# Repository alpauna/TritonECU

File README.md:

# TritonECU

Standalone engine and transmission controller for **Ford modular V8s of the
EEC-V era** — replacing the factory PCM.

Developed against a **1999 F-150 4WD, 5.4L Triton 2V, 4R70W**, but the
architecture is the modular family rather than one truck: 4.6L and 5.4L 2V
share the crank trigger, the sensor set, the SCP bus and the connector, so
Mustangs and other EEC-V modular applications of the period are the same
problem with a different calibration.

Built on an **STM32F767ZI**. Rewritten from scratch on the `rebuild` branch;
the previous ESP32-S3 firmware is described in
[`docs/legacy-esp32s3-README.md`](docs/legacy-esp32s3-README.md) and still
lives on `main`.

**What is vehicle-specific and what is not:**

| Portable across EEC-V modulars | Specific to this truck |
|---|---|
| 36-1 VR crank decode, cam sync | firing order, displacement |
| EEC-V 104-pin connector and pinout | 4R70W shift logic (4R100 differs) |
| SCP / J1850 PWM bus | 4x4 transfer case inputs |
| Ignition and injection output stages | VE and spark tables |
| Sensor conditioning and protection | |

---

## Status

| Milestone | | |
|---|---|---|
| **M0** Board bring-up | ✅ | 216 MHz, 2 MB flash, verified from the chip's own ID registers |
| **M1** Storage + config | ✅ | SD on SPI4, JSON config, persists across resets |
| **M2** Analog front end | ✅ | AD7606 reading known signals within tolerance |
| **M3** Crank sync | ◐ | decode logic proven — 10 native tests; **VR board on order**, CKP sensor + pigtail ordered |
| **M4** Cam sync | ◐ | logic proven — 6 native tests; **CMP sensor + pigtail ordered** — same connector as CKP |
| **M5** Spark output | ◐ | scheduler proven — 12 native tests |
| **M6+** Injection, closed loop, SCP, transmission | ○ | |
| **ECU carrier board** | ○ | **the largest piece left.** Fully specified in [`schematic-ecu-v1.txt`](docs/Schematics/schematic-ecu-v1.txt) — 736 lines, every part chosen — but **not yet captured as a schematic or laid out**. Envelope and the height constraint: [`carrier-envelope.md`](docs/carrier-envelope.md) |
| **Power board V1** | 🔒 | **released and frozen** — tagged `power-v1-released`, [`Schematics/README`](docs/Schematics/README.md) |
| **Power board V2** | ✅ | V1 **+ one part**: `C1` 100 nF 1206 X7R **200 V** across B+/PGND at the connector — a 19 mm² loop against D1's 131. Reviewed clean, **ready to fab** |
| **VR board V1** | ✅ | 4 channels, 2 × MAX9926 Mode A2 — reviewed clean, **fabricating** |
| **VR test rig** | ◐ | all dimensions measured; 9 of 10 parts ready to print, [STLs](hardware/vr-test-rig/stl/) + [BOM](hardware/vr-test-rig/BOM.md). Parts ordered bar the stepper |
| **VR rig firmware** | ✅ | RP2040 PIO step generator with a cranking profile — builds clean, [`firmware/`](hardware/vr-test-rig/firmware/) |
| **2N7002 driver board** | ✅ | 3.3 V → DM542 opto inputs, reviewed clean from Gerbers — [`hardware/2N7002 Driver/`](hardware/2N7002%20Driver/) |
| **Knock front end** | ◐ | **next build after the VR board** — schematic, net list and BOM drawn, [`knock-front-end-schematic.md`](docs/Schematics/knock-front-end-schematic.md) |
| **EEC-V connector** | ✅ | sourcing solved — Ranger donor + the TE controlled drawing |
| **Enclosure** | ◐ | **cabin, behind the glovebox**, connector face through the firewall — vent on the cabin side, [`enclosure.md`](docs/enclosure.md) |
| **Carrier template** | ✅ | printable measurement jig for the donor case floor — captures the mounting-boss pattern the layout is waiting on, [`hardware/carrier-template/`](hardware/carrier-template/) |
| **Harness label** | ✅ | printed plate for the always-hot battery lead and the four added pins — [STL](hardware/harness-label/stl/label.stl) + [`README`](hardware/harness-label/README.md) |
| **PSU platform** | ✅ | Z-bracket that stands the supply module off the surface — 74.5 × 92 × 51, [`hardware/psu-platform/`](hardware/psu-platform/) |

**28 native unit tests passing.** The decode, cam-sync and spark-scheduling
modules are `<stdint.h>`-only and testable without hardware — which is how M3–M5
were proven before the sensors existed.

```bash
pio test -e native              # logic, no hardware
pio run -e nucleo -t upload     # flash the board
```

## Why it is being rebuilt

The previous firmware worked, but was written against an ESP32-S3 that was
never in a truck, and one of its structural decisions turned out to be wrong:
**coils and injectors were driven through MCP23S17 SPI expanders.**

At 6000 rpm one crank degree is **27.8 µs**. An SPI transaction is several
microseconds at best, is not deterministic, and cannot be driven from a
hardware timer. Spark timing cannot live behind a port expander. That is not a
bug to patch — it changes ignition, injection and the pin map together.

Proven pieces get ported forward deliberately. Everything else earns its place
again. See [`docs/roadmap.md`](docs/roadmap.md).

## Hardware

Design is frozen — [`docs/v1-scope.md`](docs/v1-scope.md) is the build list.

**Two boards are finished.** Schematics, BOMs and Gerbers are all version
controlled in [`docs/Schematics/`](docs/Schematics/) — the fab outputs, not just
pictures of them.

| Board | Size | Review |
|---|---|---|
| **Power V1** | 76.58 × 46.74 mm, 4 layer | [`review-power-v1-bom-gerbers.md`](docs/review-power-v1-bom-gerbers.md) |
| **VR V1** | 35.43 × 33.91 mm, 2 layer | [`review-vr-v1.md`](docs/review-vr-v1.md) |

Both reviews were **measured out of the Gerbers** — copper polygon areas, via
positions, pad geometry and the flying-probe netlist — rather than read off a
render. That is how the MAX25239 footprint, Q2's thermal path and the output-cap
pour were actually checked. The earlier schematic-only pass on the power board
is [`schematic-review-power-v2.md`](docs/schematic-review-power-v2.md).

| Block | Part |
|---|---|
| MCU | STM32F767ZI (Nucleo-144 now, raw chip later) |
| Input protection | LTC4364-2 — reverse polarity, load dump, overcurrent, brownout holdup |
| Pass element | IRF540NS (D2Pak) on HGATE — planar, published SOA, 20 tented vias into 1.14 in² of B+ |
| 5 V rail | MAX25239AFF**A** buck-boost, 2.1 MHz, spread spectrum, 2.2 µH |
| 3.3 V rail | TLV62085 buck from 5 V, 2.4 MHz, 500 nH |
| ADC reference | MAX6070AAUT25, 2.5 V, gated for sleep |
| Battery sense | INA238 on the LTC4364's own 10 mΩ / 1 % / 50 ppm shunt |
| Analog in | **ADS8588H** — 8 ch, 16-bit, 500 kSPS simultaneous, ±10 V, **9 kV input clamp**, −40…+125 °C |
| Analog in *(bench)* | **Tokmas AD7606BSTZ** — same LQFP-64 footprint, 200 kSPS, already in hand |
| Crank / cam / OSS | 2 × MAX9926 Mode A2 — 4 channels, adaptive threshold + zero crossing |
| Knock | TLV9064-Q1 differential charge amp + own 2.5 V ref — [schematic](docs/Schematics/knock-front-end-schematic.md) |
| Barometric | **KP497** (Infineon) on I²C/SPI, AEC-Q100 −40…+105 °C, 3.3 V always-on rail — **requires a vented enclosure** |
| Ignition | 8 × ISL9V3040 ignition IGBT + 74HCT541 |
| Injection | 8 × ZXMS6005DGQ IntelliFET |
| SCP / J1850 PWM | **DRV8837** differential TX + **TLV7031** comparator RX — the cluster's only link to the PCM |
| Connector | EEC-V 104-pin |

### Decisions worth knowing

- **No Wi-Fi.** An always-on radio on an engine controller is a remote attack
  surface with a path to code execution via OTA. Ethernet needs physical
  access. [`docs/platform-decision.md`](docs/platform-decision.md)
- **2.1 MHz switching** to clear the AM broadcast band — a 400 kHz converter
  puts harmonics at 1.2 and 1.6 MHz, inside it. The MAX25239's `A` and `B`
  suffixes are 2100 kHz and 400 kHz respectively, and the board was nearly
  built with the wrong one.
  [`docs/always-on-domain.md`](docs/always-on-domain.md)
- **The MCU never fully powers down.** It sleeps on an always-on 3.3 V rail at
  ~3 µA and brings the rest up on demand, which removes the graceful-shutdown
  problem, replaces KAPWR and makes supply-fault latching implementable in
  firmware. Parked drain is ~950 µA, about 1 % of the battery per month.
  [`docs/always-on-domain.md`](docs/always-on-domain.md)
- **The ADC lives on a daughterboard.** Not for proximity — that is a placement
  problem — but for analog ground plane control on a board that low-side
  switches eight ignition coils, and so the front end can be respun without the
  carrier. [`docs/adc-daughterboard.md`](docs/adc-daughterboard.md)
- **The SEPIC was retired.** An integrated buck-boost deletes the external FET,
  the Schottky, both inductors and the coupling-cap bank, and adds spread
  spectrum the controller design never had.
  [`docs/power-supply.md`](docs/power-supply.md) keeps the input-chain analysis
  and marks the rest superseded.
- **Clamp both loads, dissipate neither.** A coil's flyback *is* the spark
  (400 V clamp); an injector's is waste but a plain diode makes it close
  slowly and over-fuel at idle (60–70 V clamp).
  [`docs/output-drivers.md`](docs/output-drivers.md)
- **The shunt is sensed twice and sets two things.** The LTC4364's current
  limit and the INA238's battery-current reading both come off one 10 mΩ
  resistor, so its tolerance and TCR are the accuracy of both — which is why it
  is a 1 %, ±50 ppm/°C, AEC-Q200 metal-element part in 2512 rather than
  whatever was cheapest.
- **Leave the factory harness alone.** Every "this should be referenced
  differently" question is answered by **PCB routing, not by moving wires** — the
  board defines what each of the 104 cavities connects to. An unmodified harness
  stays diagnosable by anyone with a Ford wiring diagram, and the PCB is the half
  that can be revised.
  [`docs/1999-Ford-F150-4wd-5.42v/connector-sourcing.md`](docs/1999-Ford-F150-4wd-5.42v/connector-sourcing.md)
- **The VR trigger point needs no calibration term.** MAX9926 Mode A2 arms on
  33 % of the previous peak but *triggers* on the zero crossing
  (−6.5 / +10 mV) — which is the tooth centre, because a VR sensor outputs
  dΦ/dt. Amplitude, rpm and acceleration cannot move it; scaling a waveform does
  not shift where it crosses zero. Propagation delay is 50 ns, or 0.0018° at
  6000 rpm. This repo previously had it wrong in three places, claiming the
  comparator switched at ⅓ of peak and that the offset would need characterising.
  [`docs/1999-Ford-F150-4wd-5.42v/vr-conditioning.md`](docs/1999-Ford-F150-4wd-5.42v/vr-conditioning.md)
- **MAX9926 over the LM1815, on arming margin.** Both arm adaptively and trigger
  on zero crossing, so timing is a wash. The LM1815 arms at **80 %** of the
  previous peak against the MAX9926's **33 %** — tolerating a 1.25:1 amplitude
  collapse between teeth where the MAX9926 tolerates **3:1**. Cranking, slowing
  hard against each compression stroke, is exactly where that collapse happens.
  The differential input the single-ended LM1815 cannot offer settles the rest.
- **Keyway to missing tooth is zero, on the rig and on the truck.** The bench
  wheel's keyway lines up with the gap, and the 5.4L was timed to the same datum,
  so `CKP_GAP_TO_TDC_DEG = 0` for both. It stays a *named* constant rather than a
  vanished zero — the rig's absolute angle is then the engine's absolute angle,
  which makes the rig a timing calibration bench rather than a functional check.
  [`hardware/vr-test-rig/README.md`](hardware/vr-test-rig/README.md)
- **Stiffness comes from section, not from material.** Two 8 mm rods in ribs
  under the rig's base take it from `EI` 20.5 to 826 N·m² — 40× — because the
  offset contributes `A·d²`. A 5 mm rod in a rib beats a 10 mm rod buried in the
  plate. The same arithmetic found the real soft spot: the printed bearing
  bracket was less stiff than the shaft it was holding.
  [`hardware/vr-test-rig/BOM.md`](hardware/vr-test-rig/BOM.md)
- **A printed trigger wheel produces nothing.** A VR sensor works on reluctance
  change; printed plastic is magnetically identical to air. The bench rig is
  printed, the 36-1 wheel is steel, and the cam target is a printed disc with one
  steel bolt. [`hardware/vr-test-rig/`](hardware/vr-test-rig/)
- **The knock sensor is differential, and that decides its front end.** A
  two-wire floating piezo (pins 57, 32) into a single-ended knock IC would ground
  one leg and inject sensor-ground noise straight into a microvolt signal. A
  differential charge amp is needed either way, so it is the part to build — and
  it defers the IC-versus-DSP choice rather than forcing it. One TLV9064-Q1 quad
  holds the lot: two charge amps, a difference stage and a VMID buffer.
  [`docs/knock-front-end.md`](docs/knock-front-end.md)
- **Charge mode, because the harness moves.** Read a piezo as a *voltage* and the
  cable capacitance divides the signal down — 100 pF of loom against a 1 nF
  sensor is a 10 % error that **changes if the harness is rerouted**. Read as
  *charge*, both terminals sit at a virtual ground, the cable sees no swing, and
  sensitivity stops depending on how the loom was dressed. The feedback caps then
  *are* the calibration (`Q/Cf`), which is why they are C0G and not X7R.
- **Analog blocks get their own references.** The knock front end has a 2.5 V
  reference separate from the ADC's. It does not save an amplifier though: the
  difference stage's reference leg is one arm of a resistor bridge, and CMRR
  depends on that bridge staying balanced, so it still wants a buffer between the
  reference and `R8` rather than the reference's own output impedance in series
  with one arm.
- **The enclosure must be vented, and not only for the barometer.** A sealed box
  tracks its own temperature rather than the weather, so the barometric sensor
  would be useless in one. But a sealed automotive housing also **pumps moisture
  past its own seals** — every heat cycle pushes air out, every cool-down draws it
  and whatever is near the seal back in. A vent membrane gives that breathing a
  deliberate path; the correct pressure reading is a side effect of doing the
  housing properly. **The vent goes on the cabin side** — the box straddles the
  firewall, and its connector face lives under-hood in the spray.
  [`docs/enclosure.md`](docs/enclosure.md)
- **One ADC footprint, five parts, two vendors.** AD7606 / B / C and ADS8588S / H
  are pin-for-pin in the same LQFP-64 — verified pin by pin, not assumed. So the
  part is a **populate-time choice, not a layout one**: **ADS8588H in production**
  for its 9 kV input clamp on harness-connected pins, and the **Tokmas
  AD7606BSTZ already on the bench** for development. *(The ADS9324 is not in this
  set — 16 channels, VQFN, and a 1.8 V rail this board does not have.)*
  [`docs/adc-front-end.md`](docs/adc-front-end.md)
- **A "level shifter" is not a current driver.** The DM542's step inputs are
  optocouplers wanting **14 mA**; a BSS138 + 10 kΩ bidirectional module supplies
  **0.38 mA**, and an IRF520 module is not logic-level at all — its gate threshold
  spans 2–4 V against a 3.3 V drive, so it works warm and fails cold. The answer
  is a logic-level FET *sinking* the input, with a gate pulldown so nothing moves
  while the Pico boots. [`hardware/2N7002 Driver/`](hardware/2N7002%20Driver/)
- **Model the part you are designing around, then print it.** The rig's two VR
  sensors are modelled from the *same* parameters the mount uses, so a printed
  copy held against the real sensor tests every one of those numbers at once — and
  a mismatch proves the mount wrong in the same way. Cheaper on a 20 g print than
  after the base. [`hardware/vr-test-rig/`](hardware/vr-test-rig/)
- **The MAF is a differential measurement.** It has a dedicated signal return
  separate from the ground its supply current flows in — which is the whole
  reason for the AD7606 over the MCU's own ADC.

## The reference vehicle

Every design decision traces to a factory schematic, recorded in
[`docs/1999-Ford-F150-4wd-5.42v/`](docs/1999-Ford-F150-4wd-5.42v/). Several
overturned assumptions taken from parts catalogues and forums:

| Assumed | Actually |
|---|---|
| Wasted spark, 4 coil drivers | **Coil-on-plug, 8 individual coils** |
| ECT coolant sensor | **CHT — cylinder head temperature** |
| Oil pressure sender | **A switch.** Binary, not analog |
| No knock sensor on the 2V | **Present** — C103 |
| 4R70W has a TSS | **It does not.** 4R100 only |
| GEM is on the SCP bus | **It is on ISO 9141.** Only the PCM and cluster are on SCP |

PATS is a non-issue: the anti-theft logic lives in the instrument cluster and
authorises *the PCM* over SCP. A replacement ECU never asks, so there is
nothing to defeat.

## External references — to read, not yet read

| | |
|---|---|
| [4R100 rebuild manual for the DIY](https://www.powerstrokearmy.com/threads/4r100-rebuild-manual-for-the-diy.20642/) | ⚠ **4R100, not 4R70W** — this truck has the 4R70W. Worth having anyway: the **MegaSquirt pinout this project cross-checks against was developed on a 4R100**, which is why it listed a coast clutch solenoid that does not exist here ([`output-drivers.md`](docs/output-drivers.md)). If another MS-sheet entry ever looks wrong, this is where the explanation will be |
| [Dorman 917-060 — the rig's 36-1 wheel](https://www.dormanproducts.com/p-53996-917-060.aspx) ([Amazon, with the reviews](https://www.amazon.com/Dorman-917-060-Ignition-Pulsator-Ring/dp/B00B2LCDQA)) | Steel, **35 teeth**, OE cross **XW1Z-12A227-AC**, modular V8 (2001-2010 F-150 4.6, **2002-2010 F-150 5.4**). ⚠ **Bench part only — do not fit it to the truck.** A review reports its teeth do not match the OEM wheel, giving timing codes and rough running; we measured its keyway **5.00° — half a tooth pitch — from where the factory datum was believed to be** ([`vr-test-rig/README.md`](hardware/vr-test-rig/README.md)) |

## Layout

```
firmware/ecu/
  src/core/     decode, cam sync, spark scheduling — portable, unit-tested
  src/stm32/    STM32 platform layer
  src/esp32/    ESP32-P4 platform layer (earlier target, still builds)
  test/         native unit tests
hardware/       pin budget and supply calculators
  vr-test-rig/    parametric OpenSCAD for the 36-1 + cam bench rig
  psu-enclosure/  printed box for the bench supply
  harness-label/  printed label - the always-hot lead and the added pins
  carrier-template/ measurement jig for the donor ECU case
  psu-platform/   Z-bracket platform for the supply module
docs/           design documents and vehicle schematics
  Schematics/   board schematics, BOMs and Gerbers — fab-ready
  Datasheets/   every part datasheet the decisions were made against
  1999-Ford-F150-4wd-5.42v/  Ford's own diagrams and service manual
  DonorECU/     the scrap PCM the connector and case come from
tools/          USB permission setup
```

### What gets committed, and why the repo is big

**~300 MB, and that is a deliberate trade.** The breakdown:

| | MB | |
|---|--:|---|
| Vendor datasheets | 79.8 | re-downloadable, but manufacturers pull obsolete parts |
| Ford service manual | 29.5 | **hard to re-source, and getting harder** |
| Ford scans — diagrams, connectors | 24.4 | same |
| Interactive BOMs | 22.9 | regenerable |
| Board design files | 11.9 | |
| STLs | 4.4 | regenerable from the `.scad` |
| **Source and docs — the actual project** | **1.5** | **0.9 %** |

**The thinking is 1.5 MB. Everything else is evidence.**

**Keep the evidence.** Design decisions across these documents are justified by
*"Ford's own sheet says X"*, and that phrase only means something if the sheet is
here. The archive has been re-read repeatedly to *correct* conclusions, not just
to support them — pin 64's function, the MAF's Kelvin wiring, the EPC resistance
that showed a suspect part was healthy. A 1999 service manual gets harder to find
every year.

**Do not commit regenerable artifacts.** Interactive BOMs, build outputs, export
by-products. The two BOM HTMLs predate this rule; they stay because removing them
now would not reclaim anything.

> **Why "not reclaim anything":** git keeps every blob ever committed. Deleting a
> file from the working tree shrinks the checkout, not the history. Only
> `git filter-repo` and a force-push reclaims space — and that rewrites shared
> history, invalidates the `power-v1-released` tag's SHA, and breaks every
> existing clone. **Not worth it at this size.**

**Revisit at ~700 MB.** GitHub soft-warns near 1 GB and hard-limits *individual
files* at 100 MB; the largest here is 30 MB. If it ever does need shrinking, the
lever is the **vendor datasheets at 45 %** — not the Ford material, which is the
least replaceable thing in the repository.

## Bench setup

[`docs/nucleo-setup.md`](docs/nucleo-setup.md) is a runbook for bringing a
Nucleo up from scratch, including the failures that actually cost time — the
ST-Link udev rule, programming the ELF rather than the `.bin`, and
`-Wl,-u,_printf_float`.

```bash
tools/setup-usb-permissions.sh      # debug probe access
```

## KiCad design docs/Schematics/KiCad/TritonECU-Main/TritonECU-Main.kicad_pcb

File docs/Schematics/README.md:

# Board files — which revision is which

| Board | Rev | State | Files |
|---|---|---|---|
| **Power** | **V1** | 🔒 **RELEASED — frozen, do not edit** | `*_Power_V_1.*`, `TritonECU_Power_V_1_Gerber.zip`, `TritonECU_Power_InteractiveBOM-V1.html` |
| **Power** | **V2** | 🟢 **current** | `*_Power_V_2.*`, `TritonECU_Power_V_2_Gerber.zip`, `TritonECU_Power_InteractiveBOM-V2.html` |
| **VR** | V1 | 🟢 current | `TritonECU_VR_*_V_1.*` |

**V1 is frozen because it has been released.** Design changes go to V2. The only
edits V1 should ever receive are **corrections to its own record** — see below.

## Power V2 — the delta is one part

A part census (immune to designator renumbering) gives **exactly one addition**:

| | |
|---|---|
| **C1** | **100 nF, `CGA1206X7R104K201MT`** — 1206 X7R, automotive CGA, **200 V** |

Everything else is identical. The capacitor designators *appear* to have changed
wholesale between the two BOMs, but that is the tool **renumbering the sequence**
when C1 was inserted — every part shifted up, none changed.

### Why it is there

`B+` had **no capacitor at all** in V1 — it touched only CN1, D1, Q1 and three
divider resistors, with the nearest component of any kind 8 mm away. A TVS is a
slow device dressed as a fast one: **D1 does nothing until 43 V and then has to
turn on, while a capacitor has no threshold.** The cap takes the *edge*, the TVS
takes the *energy*. See [`../review-power-v1-bom-gerbers.md`](../review-power-v1-bom-gerbers.md).

### ✅ And it is placed properly, which is what actually decides the benefit

Measured off the V2 netlist:

```
  CN1_1 B+   (12.19, 6.22)        C1_2 B+   (13.39, 9.91)
  CN1_2 PGND (17.27, 6.22)        C1_1 PGND (16.58, 9.91)
```

| | Loop | vs D1 |
|---|--:|--:|
| **C1** | **5.08 × 3.69 mm = 19 mm²** | **7× smaller** |
| D1 | 17.7 × 7.4 mm = 131 mm² | — |

Which is worth **2.4–2.7×** on fast-edge overshoot — 33–75 V on ISO 7637-2 pulse
3a/3b where D1 alone gives 80–200 V. **200 V is more headroom than the 100 V that
was asked for**, and 1206 is what a 200 V X7R at 100 nF needs; its extra ~0.2 nH
of ESL is nothing against a 7–18 nH loop.

## ⚠ One thing to check on any V1 boards already built

The V1 BOM was re-exported and **corrected** — the original export was
column-shifted, which put the manufacturer in the part field, leaked a footprint
string into the designator column as a phantom part, and listed `D2` twice with
two different components. Correcting that is legitimate on a frozen revision,
because it makes V1's record match the V1 *board*.

**But two entries are part substitutions rather than corrections**, and if V1
hardware was assembled from the original BOM it will not match:

| Ref | Original V1 BOM | V1 BOM now, and V2 |
|---|---|---|
| **R1** | `FRM252WJR010TN` | `FPM253WFR010TM` |
| **Q4** | `BS170FTA` | `BSS123` |

**[CONFIRM]** which parts are actually fitted to any assembled V1 board. Both
swaps keep the footprint, so either part fits — the BOM cannot tell you which one
went on.

## Recovering an exact released state

The filenames carry the revision, but **a git tag is the reliable handle**:

```bash
git tag -l 'power-v*'            # what has been released
git show power-v1                # the tree as released
```

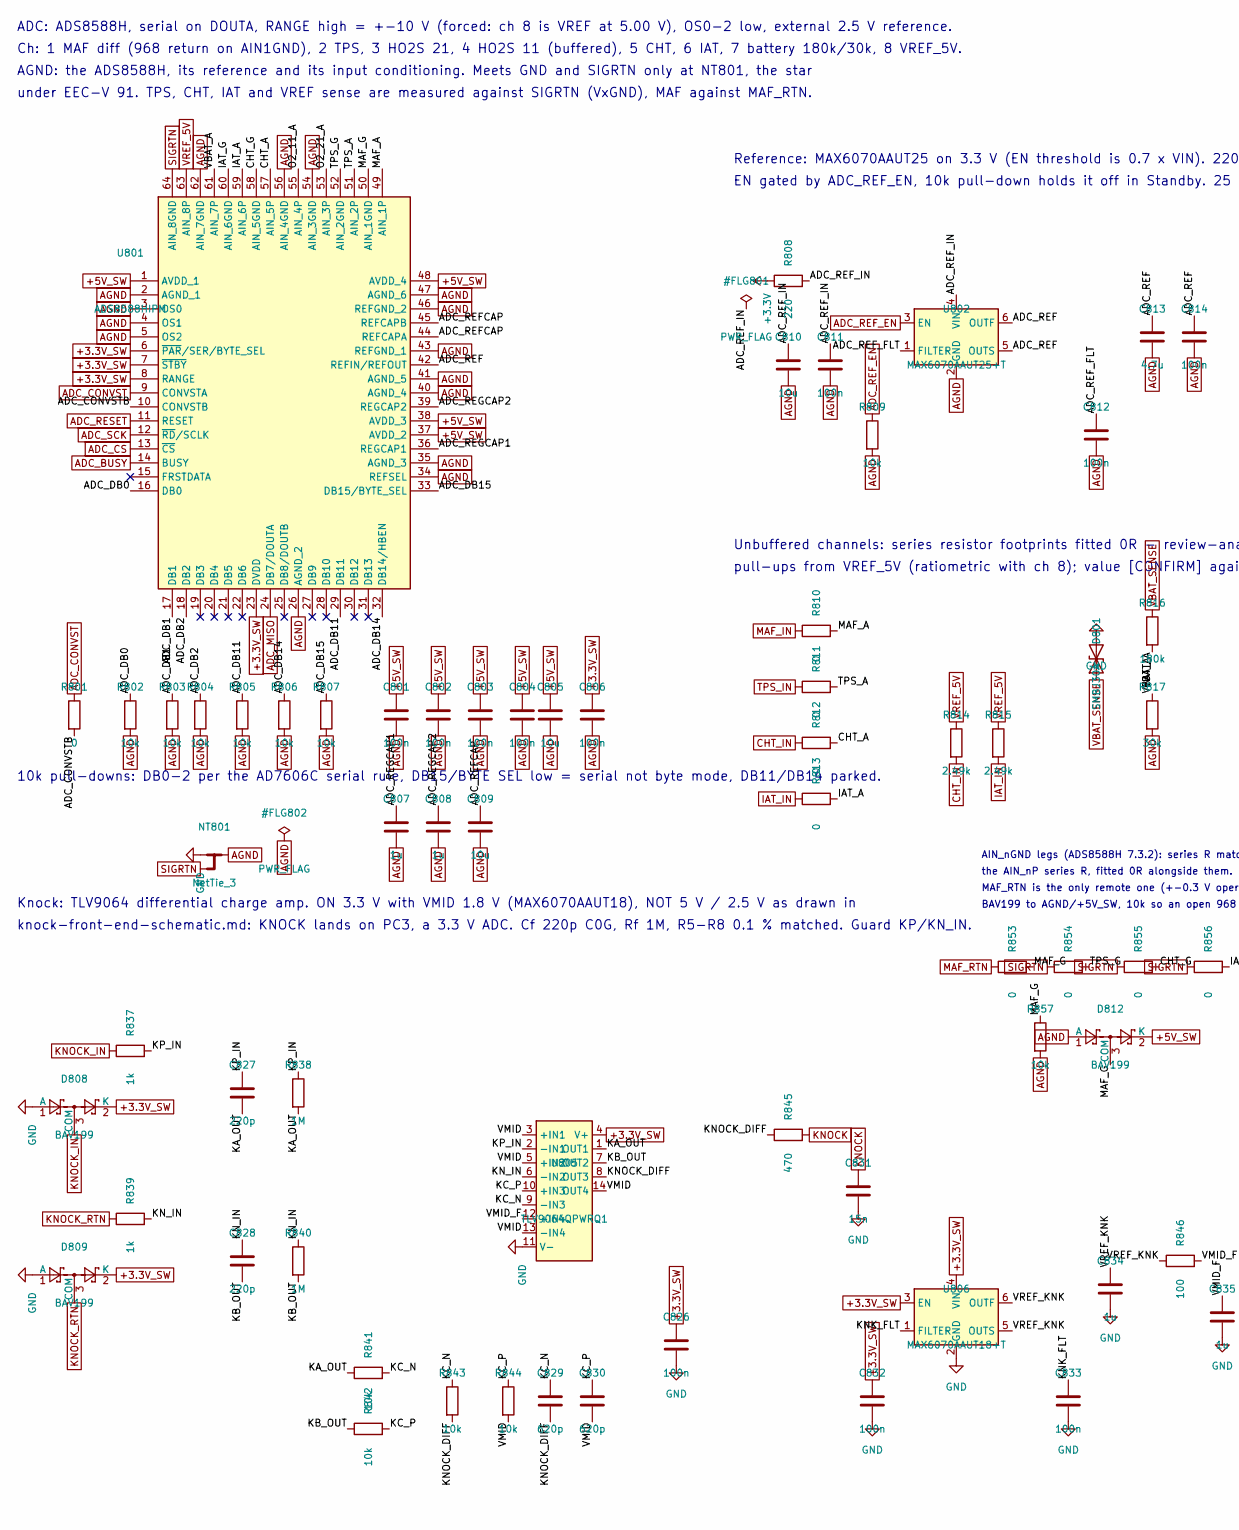
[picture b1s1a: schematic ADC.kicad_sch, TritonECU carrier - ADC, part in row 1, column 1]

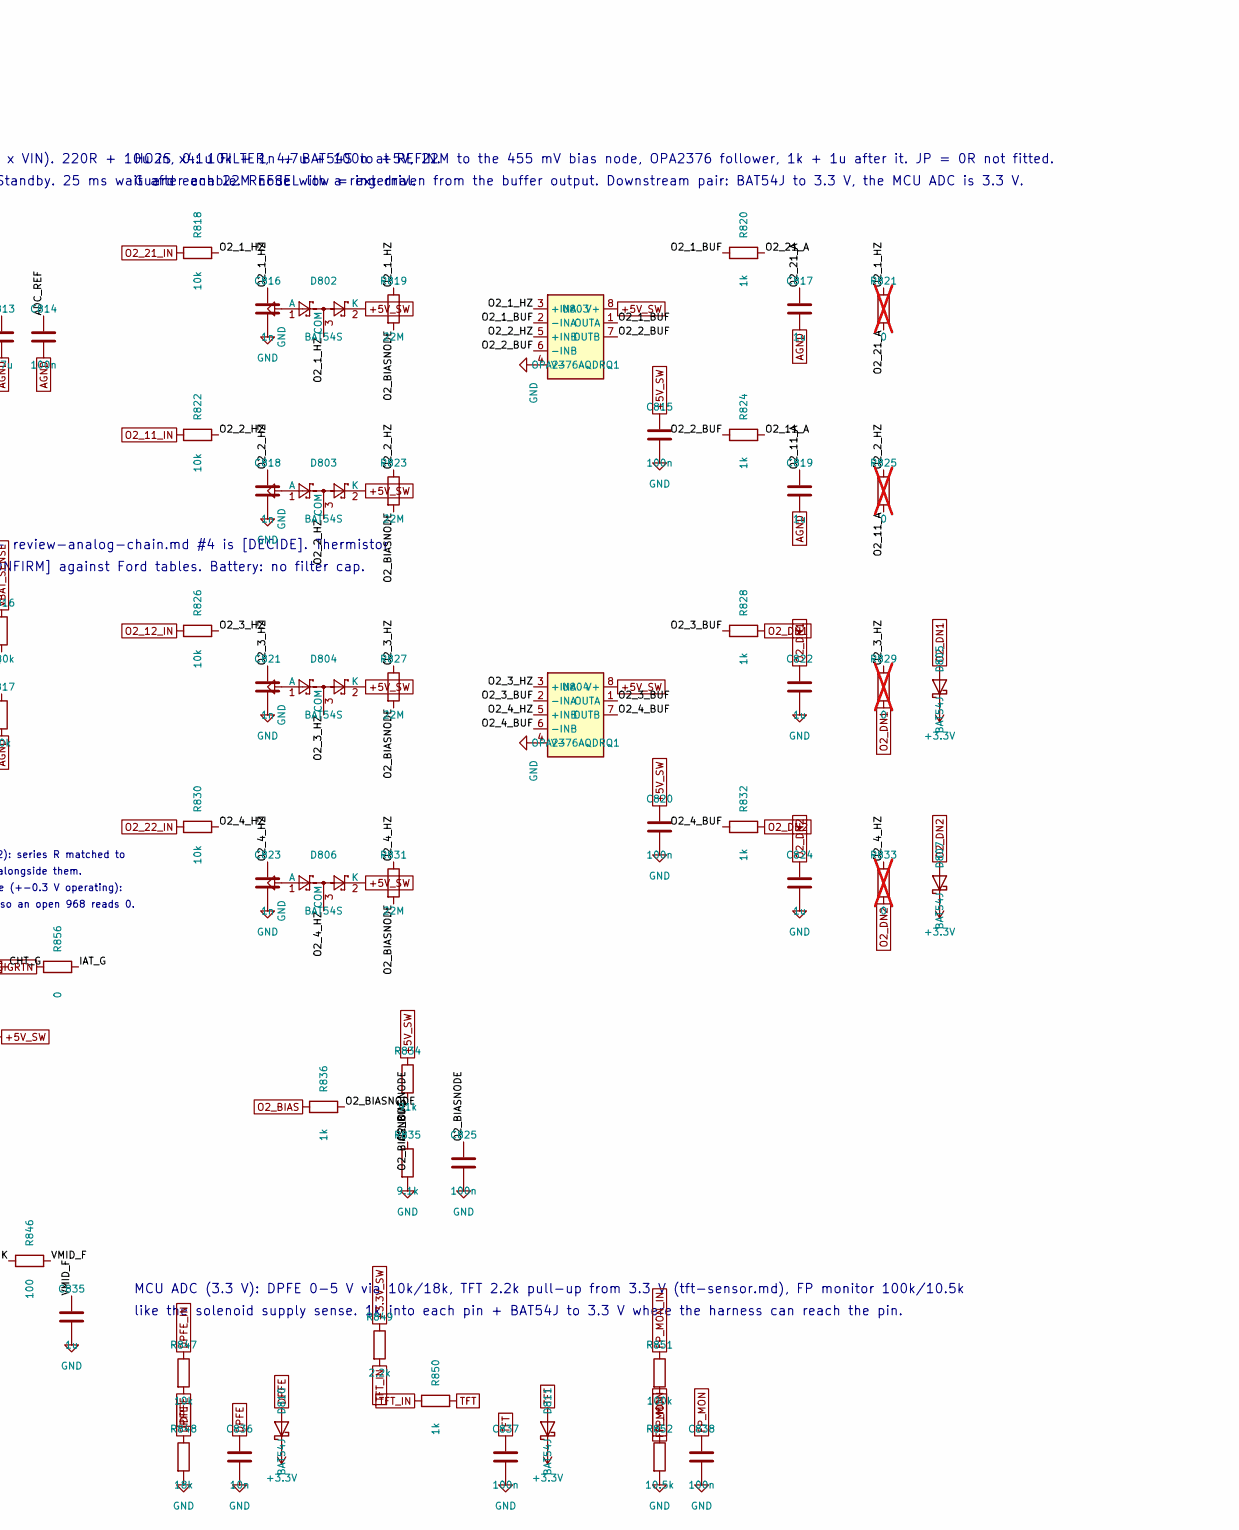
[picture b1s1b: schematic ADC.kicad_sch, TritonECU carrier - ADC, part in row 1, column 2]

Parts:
C801, C802, C803, C804, C806, C811, C812, C814, C815, C820, C825, C826, C832, C833, C837, C838: 100n; C_0603_1608Metric_Pad1.08x0.95mm_HandSolder
C805, C809, C810: 10u; C_0805_2012Metric_Pad1.18x1.45mm_HandSolder
C807, C808, C817, C819, C822, C824, C834, C835: 1u; C_0603_1608Metric_Pad1.08x0.95mm_HandSolder
C813: 4.7u; C_0805_2012Metric_Pad1.18x1.45mm_HandSolder
C816, C818, C821, C823: 1n; C_0603_1608Metric_Pad1.08x0.95mm_HandSolder
C827, C828: 220p; C_0603_1608Metric_Pad1.08x0.95mm_HandSolder
C829, C830: 620p; C_0603_1608Metric_Pad1.08x0.95mm_HandSolder
C831: 15n; C_0603_1608Metric_Pad1.08x0.95mm_HandSolder
C836: 10n; C_0603_1608Metric_Pad1.08x0.95mm_HandSolder
D801: SMBJ30A; D_SMB
D802, D803, D804, D806: BAT54S; SOT-23
D805, D807, D810, D811: BAT54J; D_SOD-323F
D808, D809, D812: BAV199; SOT-23
NT801: NetTie_3; NetTie-3_SMD_Pad0.5mm
R801, R810, R811, R812, R813, R853, R854, R855, R856: 0; R_0603_1608Metric_Pad0.98x0.95mm_HandSolder
R802, R803, R804, R805, R806, R807, R809, R841, R842, R843, R844, R847, R857: 10k; R_0603_1608Metric_Pad0.98x0.95mm_HandSolder
R808: 220; R_0603_1608Metric_Pad0.98x0.95mm_HandSolder
R814, R815: 2.49k; R_0603_1608Metric_Pad0.98x0.95mm_HandSolder
R816: 180k; R_0603_1608Metric_Pad0.98x0.95mm_HandSolder
R817: 30k; R_0603_1608Metric_Pad0.98x0.95mm_HandSolder
R818, R822, R826, R830: 10k; R_0805_2012Metric_Pad1.20x1.40mm_HandSolder
R819, R823, R827, R831: 22M; R_0805_2012Metric_Pad1.20x1.40mm_HandSolder
R820, R824, R828, R832, R836, R837, R839, R850: 1k; R_0603_1608Metric_Pad0.98x0.95mm_HandSolder
R821, R825, R829, R833: 0; R_0603_1608Metric_Pad0.98x0.95mm_HandSolder; not fitted
R834: 91k; R_0603_1608Metric_Pad0.98x0.95mm_HandSolder
R835: 9.1k; R_0603_1608Metric_Pad0.98x0.95mm_HandSolder
R838, R840: 1M; R_0603_1608Metric_Pad0.98x0.95mm_HandSolder
R845: 470; R_0603_1608Metric_Pad0.98x0.95mm_HandSolder
R846: 100; R_0603_1608Metric_Pad0.98x0.95mm_HandSolder
R848: 18k; R_0603_1608Metric_Pad0.98x0.95mm_HandSolder
R849: 2.2k; R_0603_1608Metric_Pad0.98x0.95mm_HandSolder
R851: 100k; R_0603_1608Metric_Pad0.98x0.95mm_HandSolder
R852: 10.5k; R_0603_1608Metric_Pad0.98x0.95mm_HandSolder
U801: ADS8588HIPM; QFP50P1200X1200X160-64N
U802: MAX6070AAUT25+T; SOT-23-6
U803, U804: OPA2376AQDRQ1; SOIC-8_3.9x4.9mm_P1.27mm
U805: TLV9064QPWRQ1; TSSOP-14_4.4x5mm_P0.65mm
U806: MAX6070AAUT18+T; SOT-23-6

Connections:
+3.3V: D805.1 (K), D807.1 (K), D810.1 (K), D811.1 (K), R808.1; also elsewhere on the board
+3.3V_SW: C806.1, C826.1, C832.1, D808.2 (K), D809.2 (K), R849.1, U801.6 (~PAR/SER/BYTE_SEL), U801.7 (~STBY), U801.8 (RANGE), U801.23 (DVDD), U805.4 (V+), U806.3 (EN), U806.4 (VIN); also elsewhere on the board
+5V_SW: C801.1, C802.1, C803.1, C804.1, C805.1, C815.1, C820.1, D802.2 (K), D803.2 (K), D804.2 (K), D806.2 (K), D812.2 (K), R834.1, U801.1 (AVDD_1), U801.37 (AVDD_2), U801.38 (AVDD_3), U801.48 (AVDD_4), U803.8 (V+), U804.8 (V+); also elsewhere on the board
/ADC/ADC_CONVSTB: R801.2, U801.10 (CONVSTB)
/ADC/ADC_DB0: R802.1, U801.16 (DB0)
/ADC/ADC_DB1: R803.1, U801.17 (DB1)
/ADC/ADC_DB2: R804.1, U801.18 (DB2)
/ADC/ADC_DB11: R805.1, U801.29 (DB11)
/ADC/ADC_DB14: R806.1, U801.32 (DB14/HBEN)
/ADC/ADC_DB15: R807.1, U801.33 (DB15/BYTE_SEL)
/ADC/ADC_REF: C813.1, C814.1, U801.42 (REFIN/REFOUT), U802.5 (OUTS), U802.6 (OUTF)
/ADC/ADC_REFCAP: C809.1, U801.44 (REFCAPA), U801.45 (REFCAPB)
/ADC/ADC_REF_FLT: C812.1, U802.1 (FILTER)
/ADC/ADC_REF_IN: C810.1, C811.1, R808.2, U802.4 (VIN)
/ADC/ADC_REGCAP1: C807.1, U801.36 (REGCAP1)
/ADC/ADC_REGCAP2: C808.1, U801.39 (REGCAP2)
/ADC/CHT_A: R812.2, U801.57 (AIN_5P)
/ADC/CHT_G: R855.2, U801.58 (AIN_5GND)
/ADC/IAT_A: R813.2, U801.59 (AIN_6P)
/ADC/IAT_G: R856.2, U801.60 (AIN_6GND)
/ADC/KA_OUT: C827.2, R838.2, R841.1, U805.1 (OUT1)
/ADC/KB_OUT: C828.2, R840.2, R842.1, U805.7 (OUT2)
/ADC/KC_N: C829.1, R841.2, R843.1, U805.9 (-IN3)
/ADC/KC_P: C830.1, R842.2, R844.1, U805.10 (+IN3)
/ADC/KNK_FLT: C833.1, U806.1 (FILTER)
/ADC/KNOCK_DIFF: C829.2, R843.2, R845.1, U805.8 (OUT3)
/ADC/KN_IN: C828.1, R839.2, R840.1, U805.6 (-IN2)
/ADC/KP_IN: C827.1, R837.2, R838.1, U805.2 (-IN1)
/ADC/MAF_A: R810.2, U801.49 (AIN_1P)
/ADC/MAF_G: D812.3 (COM), R853.2, R857.1, U801.50 (AIN_1GND)
/ADC/O2_1_BUF: R820.1, U803.1 (OUTA), U803.2 (-INA)
/ADC/O2_1_HZ: C816.1, D802.3 (COM), R818.2, R819.1, R821.1, U803.3 (+INA)
/ADC/O2_2_BUF: R824.1, U803.6 (-INB), U803.7 (OUTB)
/ADC/O2_2_HZ: C818.1, D803.3 (COM), R822.2, R823.1, R825.1, U803.5 (+INB)
/ADC/O2_3_BUF: R828.1, U804.1 (OUTA), U804.2 (-INA)
/ADC/O2_3_HZ: C821.1, D804.3 (COM), R826.2, R827.1, R829.1, U804.3 (+INA)
/ADC/O2_4_BUF: R832.1, U804.6 (-INB), U804.7 (OUTB)
/ADC/O2_4_HZ: C823.1, D806.3 (COM), R830.2, R831.1, R833.1, U804.5 (+INB)
/ADC/O2_11_A: C819.1, R824.2, R825.2, U801.55 (AIN_4P)
/ADC/O2_21_A: C817.1, R820.2, R821.2, U801.53 (AIN_3P)
/ADC/O2_BIASNODE: C825.1, R819.2, R823.2, R827.2, R831.2, R834.2, R835.1, R836.2
/ADC/TPS_A: R811.2, U801.51 (AIN_2P)
/ADC/TPS_G: R854.2, U801.52 (AIN_2GND)
/ADC/VBAT_A: R816.2, R817.1, U801.61 (AIN_7P)
/ADC/VMID: C830.2, R844.2, U805.3 (+IN1), U805.5 (+IN2), U805.13 (-IN4), U805.14 (OUT4)
/ADC/VMID_F: C835.1, R846.2, U805.12 (+IN4)
/ADC/VREF_KNK: C834.1, R846.1, U806.5 (OUTS), U806.6 (OUTF)
ADC_BUSY: U801.14 (BUSY); also elsewhere on the board
ADC_CONVST: R801.1, U801.9 (CONVSTA); also elsewhere on the board
ADC_CS: U801.13 (~CS); also elsewhere on the board
ADC_MISO: U801.24 (DB7/DOUTA); also elsewhere on the board
ADC_REF_EN: R809.1, U802.3 (EN); also elsewhere on the board
ADC_RESET: U801.11 (RESET); also elsewhere on the board
ADC_SCK: U801.12 (~RD/SCLK); also elsewhere on the board
AGND: C801.2, C802.2, C803.2, C804.2, C805.2, C806.2, C807.2, C808.2, C809.2, C810.2, C811.2, C812.2, C813.2, C814.2, C817.2, C819.2, D812.1 (A), NT801.2, R802.2, R803.2, R804.2, R805.2, R806.2, R807.2, R809.2, R817.2, R857.2, U801.2 (AGND_1), U801.3 (OS0), U801.4 (OS1), U801.5 (OS2), U801.26 (AGND_2), U801.34 (REFSEL), U801.35 (AGND_3), U801.40 (AGND_4), U801.41 (AGND_5), U801.43 (REFGND_1), U801.46 (REFGND_2), U801.47 (AGND_6), U801.54 (AIN_3GND), U801.56 (AIN_4GND), U801.62 (AIN_7GND), U802.2 (GND)
CHT_IN: R812.1, R814.2; also elsewhere on the board
DPFE: C836.1, D810.2 (A), R847.2, R848.1; also elsewhere on the board
DPFE_IN: R847.1; also elsewhere on the board
FP_MON: C838.1, R851.2, R852.1; also elsewhere on the board
FP_MON_IN: R851.1; also elsewhere on the board
GND: C815.2, C816.2, C818.2, C820.2, C821.2, C822.2, C823.2, C824.2, C825.2, C826.2, C831.2, C832.2, C833.2, C834.2, C835.2, C836.2, C837.2, C838.2, D801.2 (A2), D802.1 (A), D803.1 (A), D804.1 (A), D806.1 (A), D808.1 (A), D809.1 (A), NT801.1, R835.2, R848.2, R852.2, U803.4 (V-), U804.4 (V-), U805.11 (V-), U806.2 (GND); also elsewhere on the board
IAT_IN: R813.1, R815.2; also elsewhere on the board
KNOCK: C831.1, R845.2; also elsewhere on the board
KNOCK_IN: D808.3 (COM), R837.1; also elsewhere on the board
KNOCK_RTN: D809.3 (COM), R839.1; also elsewhere on the board
MAF_IN: R810.1; also elsewhere on the board
MAF_RTN: R853.1; also elsewhere on the board
O2_11_IN: R822.1; also elsewhere on the board
O2_12_IN: R826.1; also elsewhere on the board
O2_21_IN: R818.1; also elsewhere on the board
O2_22_IN: R830.1; also elsewhere on the board
O2_BIAS: R836.1; also elsewhere on the board
O2_DN1: C822.1, D805.2 (A), R828.2, R829.2; also elsewhere on the board
O2_DN2: C824.1, D807.2 (A), R832.2, R833.2; also elsewhere on the board
SIGRTN: NT801.3, R854.1, R855.1, R856.1, U801.64 (AIN_8GND); also elsewhere on the board
TFT: C837.1, D811.2 (A), R850.2; also elsewhere on the board
TFT_IN: R849.2, R850.1; also elsewhere on the board
TPS_IN: R811.1; also elsewhere on the board
VBAT_SENSE: D801.1 (A1), R816.1; also elsewhere on the board
VREF_5V: R814.1, R815.1, U801.63 (AIN_8P); also elsewhere on the board

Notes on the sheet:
ADC: ADS8588H, serial on DOUTA, RANGE high = +-10 V (forced: ch 8 is VREF at 5.00 V), OS0-2 low, external 2.5 V reference.
Ch: 1 MAF diff (968 return on AIN1GND), 2 TPS, 3 HO2S 21, 4 HO2S 11 (buffered), 5 CHT, 6 IAT, 7 battery 180k/30k, 8 VREF_5V.
AGND: the ADS8588H, its reference and its input conditioning. Meets GND and SIGRTN only at NT801, the star
under EEC-V 91. TPS, CHT, IAT and VREF sense are measured against SIGRTN (VxGND), MAF against MAF_RTN.
10k pull-downs: DB0-2 per the AD7606C serial rule, DB15/BYTE SEL low = serial not byte mode, DB11/DB14 parked.
Reference: MAX6070AAUT25 on 3.3 V (EN threshold is 0.7 x VIN). 220R + 10u in, 0.1u FILTER, 4.7u + 100n at REFIN.
EN gated by ADC_REF_EN, 10k pull-down holds it off in Standby. 25 ms wait after enable. REFSEL low = external.
Unbuffered channels: series resistor footprints fitted 0R - review-analog-chain.md #4 is [DECIDE]. Thermistor
pull-ups from VREF_5V (ratiometric with ch 8); value [CONFIRM] against Ford tables. Battery: no filter cap.
HO2S x4: 10k + 1n + BAT54S to +5V, 22M to the 455 mV bias node, OPA2376 follower, 1k + 1u after it. JP = 0R not fitted.
Guard each 22M node with a ring driven from the buffer output. Downstream pair: BAT54J to 3.3 V, the MCU ADC is 3.3 V.
Knock: TLV9064 differential charge amp. ON 3.3 V with VMID 1.8 V (MAX6070AAUT18), NOT 5 V / 2.5 V as drawn in
knock-front-end-schematic.md: KNOCK lands on PC3, a 3.3 V ADC. Cf 220p C0G, Rf 1M, R5-R8 0.1 % matched. Guard KP/KN_IN.
MCU ADC (3.3 V): DPFE 0-5 V via 10k/18k, TFT 2.2k pull-up from 3.3 V (tft-sensor.md), FP monitor 100k/10.5k
like the solenoid supply sense. 1k into each pin + BAT54J to 3.3 V where the harness can reach the pin.
AIN_nGND legs (ADS8588H 7.3.2): series R matched to
the AIN_nP series R, fitted 0R alongside them.
MAF_RTN is the only remote one (+-0.3 V operating):
BAV199 to AGND/+5V_SW, 10k so an open 968 reads 0.
